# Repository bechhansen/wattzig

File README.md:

# WattZig - The Open Zigbee Power Meter

A Zigbee-based smart power meter reader for ESP32C6 that reads 3-phase electrical data via DLMS protocol and reports measurements to Zigbee hubs (Home Assistant, etc.).

## Overview

WattZig reads meter data via DLMS protocol over UART and reports 3-phase electrical measurements (voltage, current, active/reactive power, power factor, energy counters) through ZHA-compliant Zigbee clusters.

*The WattZig device reporting real-time electrical measurements to Home Assistant via Zigbee. All three phases show voltage (~228-230V), current (0.0-0.7A), power (9.0-130W), and power factor (11%-86%). The device also reports total energy consumption (34,351.77 kWh delivered) and can be integrated into automations and dashboards.*

## Features

- **3-Phase Metering**: Voltage, current, active/reactive power, power factor (phases A, B, C)
- **Energy Tracking**: Import/export energy counters with reporting
- **Zigbee ZHA**: Home Assistant integration via standard clusters
- **DLMS Parser**: State machine-based protocol handler at 2400 baud
- **Low Power**: FreeRTOS task design with Zigbee sleep support
- **Auto-Commissioning**: Network steering on first start
- **Status LEDs**: Green (data transmission), Red (commissioning)
- **Button Controls**: Long press (4s) = factory reset, double-click = restart

## Hardware Requirements

- **Microcontroller**: ESP32C6 (required for Zigbee)
- **ESP-IDF**: v5.5.2 (exact version)
- **Power Supply**: ≥4.5V input, MCP1700-3302E 3.3V regulator, 470µF–1000µF bulk capacitor (parallel to regulator)
- **UART1** (DLMS): TX=GPIO0, RX=GPIO1, 2400 baud, 8 bits, no parity
- **Peripherals**: GPIO5=Red LED, GPIO6=Green LED, GPIO4=Button

See [HARDWARE.md](HARDWARE.md) for complete Bill of Materials, schematics, and assembly instructions.

## Software Requirements

- **ESP-IDF v5.5.2**: `git clone -b v5.5.2 https://github.com/espressif/esp-idf.git && ./install.sh && source export.sh`
- **Dependencies** (auto-installed):
  - `espressif/esp-zigbee-lib` (~1.6.8)
  - `espressif/esp-zboss-lib` (~1.6.4)
  - `espressif/button` (2.4.1)

## Installation & Setup

1. **Clone and configure:**
   ```bash
   git clone <repo-url>
   cd wattzig/Software
   idf.py menuconfig
   ```

2. **Required menuconfig settings:**
   - `Component Config > Zigbee > Enable Zigbee Stack`
   - `Component Config > Zigbee > Device Type > End Device`
   - `Component Config > Power Management > Enable Power Management`

3. **Build and flash:**
   ```bash
   idf.py build
   idf.py -p /dev/ttyUSB0 -b 115200 flash
   idf.py -p /dev/ttyUSB0 monitor  # Exit: Ctrl+T then X
   ```

   See [FLASHING.md](FLASHING.md) for detailed hardware setup, boot mode configuration, and troubleshooting.

## Usage

**First Start:**
1. Device boots and performs factory reset
2. LED blinks (commissioning mode)
3. Device joins nearest Zigbee network via network steering
4. LED on briefly, then off
5. UART task starts reading meter data

**Normal Operation:**
- Device loads saved network config
- UART reads DLMS frames from meter
- Parsed data updates Zigbee cluster attributes
- Energy counters trigger ZCL reports

**Zigbee Endpoint 10:**
- Basic Cluster (0x0000): Device info
- Identify Cluster (0x0003): Identification
- Electrical Measurement (0x0B04): Voltage, current, power, power factor (all phases)
- Metering Cluster (0x0702): Energy delivered/received

## Configuration

Edit [Software/main/main.h](Software/main/main.h) for:
```c
#define ENDPOINT_ID 10                    // Zigbee endpoint
#define UART_NUM UART_NUM_1               // UART peripheral
#define UART_BAUD_RATE 2400               // Meter communication speed
#define LED_PIN 5                         // Red status LED
#define LED_PIN2 6                        // Green status LED
#define ED_AGING_TIMEOUT ESP_ZB_ED_AGING_TIMEOUT_64MIN
#define ED_KEEP_ALIVE 3000                // Keep-alive interval (ms)
```

## Debugging

### Enable Debug Logging
```c
// In app_main(), modify:
esp_log_level_set("Parser", ESP_LOG_DEBUG);  // Enable DLMS parser logs
esp_log_level_set("*", ESP_LOG_INFO);         // General logs
```

## References

- [ESP-IDF v5.5.2 Documentation](https://docs.espressif.com/projects/esp-idf/en/v5.5.2/)
- [Zigbee Cluster Library (ZCL)](https://zigbeealliance.org/)
- [Zigbee Cluster Library Specification](https://zigbeealliance.org/wp-content/uploads/2019/12/07-5123-06-zigbee-cluster-library-specification.pdf)
- [DLMS/COSEM Protocol](https://www.dlms.com/)
- [Home Assistant ZHA Integration](https://www.home-assistant.io/integrations/zha/)

## License

This project is licensed under the **GNU General Public License v3 (GPLv3)**.

You are free to use, modify, and distribute this software under the following conditions:
- Any derivative works must also be released under GPLv3
- You must provide access to the source code
- You must include this license and attribution
- You cannot create proprietary closed-source versions

See [LICENSE](LICENSE) for full details.

**GPLv3 ensures that improvements and modifications remain open source for the entire community.**

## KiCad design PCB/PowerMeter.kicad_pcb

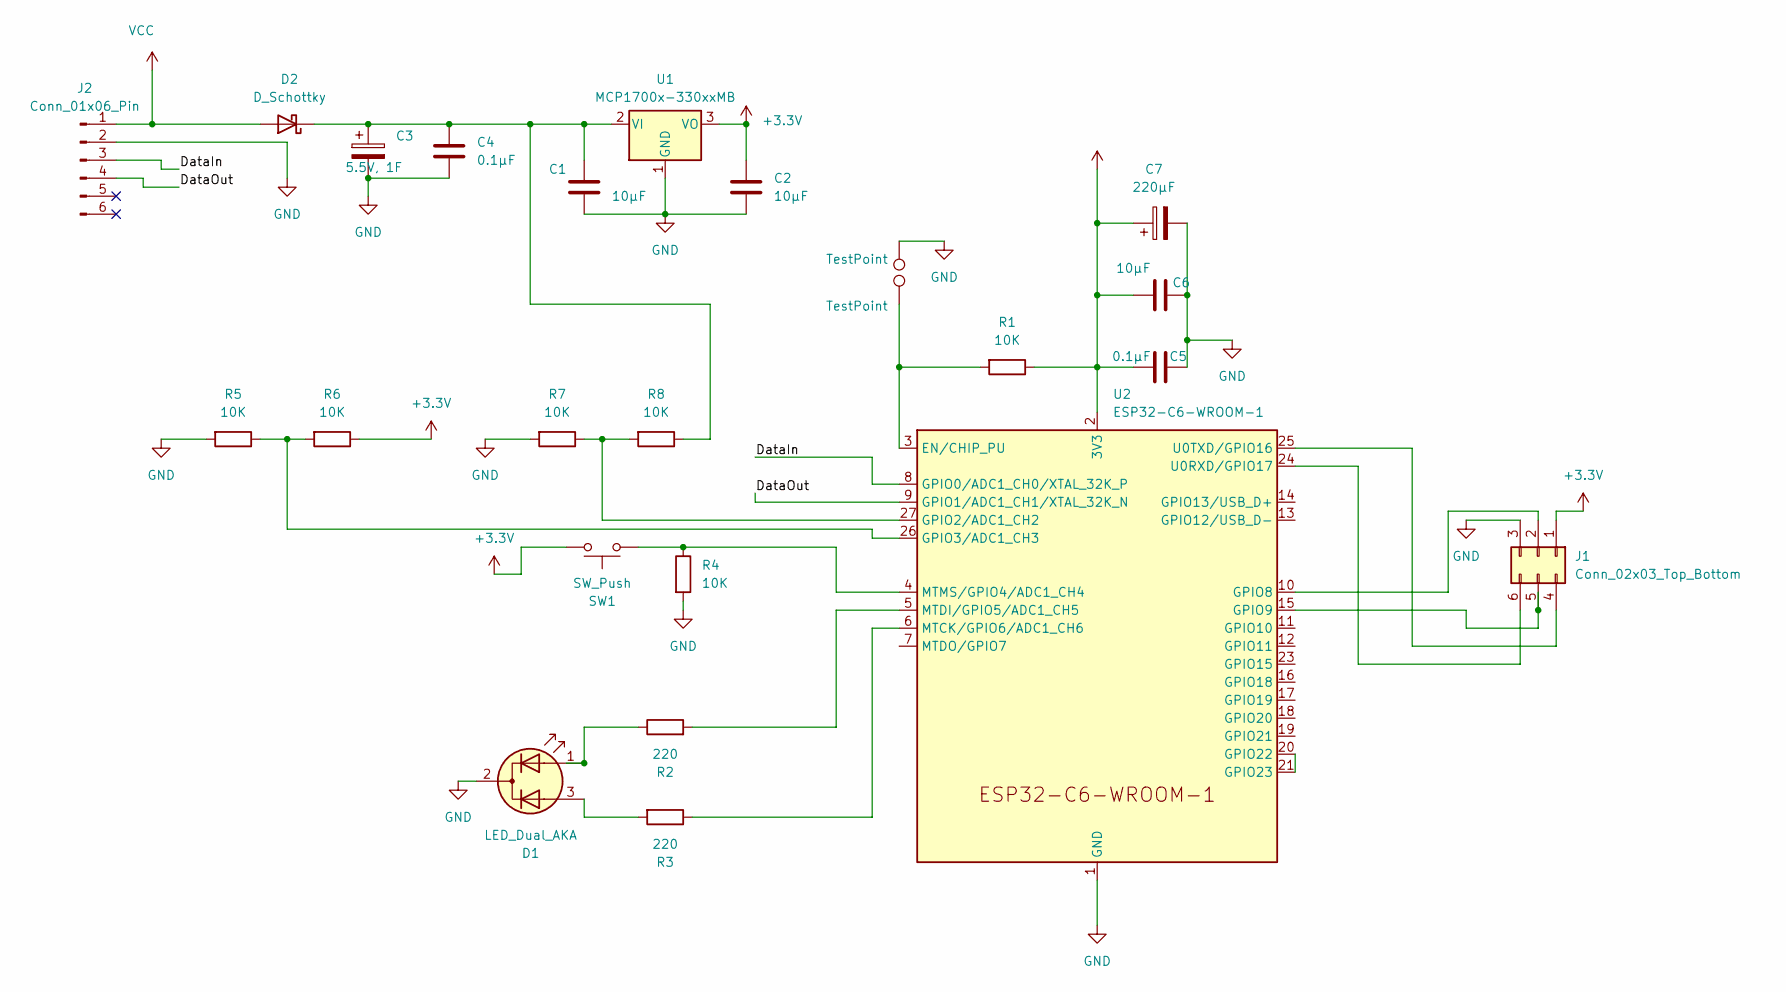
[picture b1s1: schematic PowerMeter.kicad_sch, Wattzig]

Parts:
C1, C2, C6: 10μF; C_0805_2012Metric_Pad1.18x1.45mm_HandSolder
C3: 5.5V, 1F; PHV-5R4H155-R
C4, C5: 0.1μF; C_0805_2012Metric_Pad1.18x1.45mm_HandSolder
C7: 220µF; C_1812_4532Metric
D1: LED_Dual_AKA; LED_D5.0mm-3
D2: D_Schottky; Nexperia_CFP3_SOD-123W
J1: Conn_02x03_Top_Bottom; PinHeader_2x03_P2.54mm_Vertical
J2: Conn_01x06_Pin; PinSocket_2x03_P2.54mm_Horizontal
R1, R4, R5, R6, R7, R8: 10K; R_0805_2012Metric_Pad1.20x1.40mm_HandSolder
R2, R3: 220; R_0805_2012Metric_Pad1.20x1.40mm_HandSolder
RST1, RST2: TestPoint; TestPoint_Pad_D2.0mm
SW1: SW_Push; CS1102V1135F160_pbh
U1: MCP1700x-330xxMB; SOT-89-3
U2: ESP32-C6-WROOM-1

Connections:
+3.3V: C2.1, C5.1, C6.1, C7.1, J1.1, R1.1, R6.1, SW1.1, U1.3 (VO), U2.2 (3V3)
/DataIn: J2.3, U2.8 (GPIO0/ADC1_CH0/XTAL_32K_P)
/DataOut: J2.4, U2.9 (GPIO1/ADC1_CH1/XTAL_32K_N)
GND: C1.2, C2.2, C3.2, C4.2, C5.2, C6.2, C7.2, D1.2 (K), J1.3, J2.2, R4.2, R5.2, R7.2, RST1.1, U1.1 (GND), U2.1 (GND), U2.28 (GND), U2.29 (GND)
unnamed: D1.1 (A1), R2.1
unnamed: D1.3 (A2), R3.2
unnamed: C1.1, C3.1, C4.1, D2.1 (K), R8.1, U1.2 (VI)
unnamed: J1.2, U2.10 (GPIO8)
unnamed: J1.4, U2.25 (U0TXD/GPIO16)
unnamed: J1.5, U2.15 (GPIO9)
unnamed: J1.6, U2.24 (U0RXD/GPIO17)
unnamed: R1.2, RST2.1, U2.3 (EN/CHIP_PU)
unnamed: R7.1, R8.2, U2.27 (GPIO2/ADC1_CH2)
unnamed: R5.1, R6.2, U2.26 (GPIO3/ADC1_CH3)
unnamed: U2.20 (GPIO22), U2.21 (GPIO23)
unnamed: R3.1, U2.6 (MTCK/GPIO6/ADC1_CH6)
unnamed: R2.2, U2.5 (MTDI/GPIO5/ADC1_CH5)
unnamed: R4.1, SW1.2, U2.4 (MTMS/GPIO4/ADC1_CH4)
VCC: D2.2 (A), J2.1

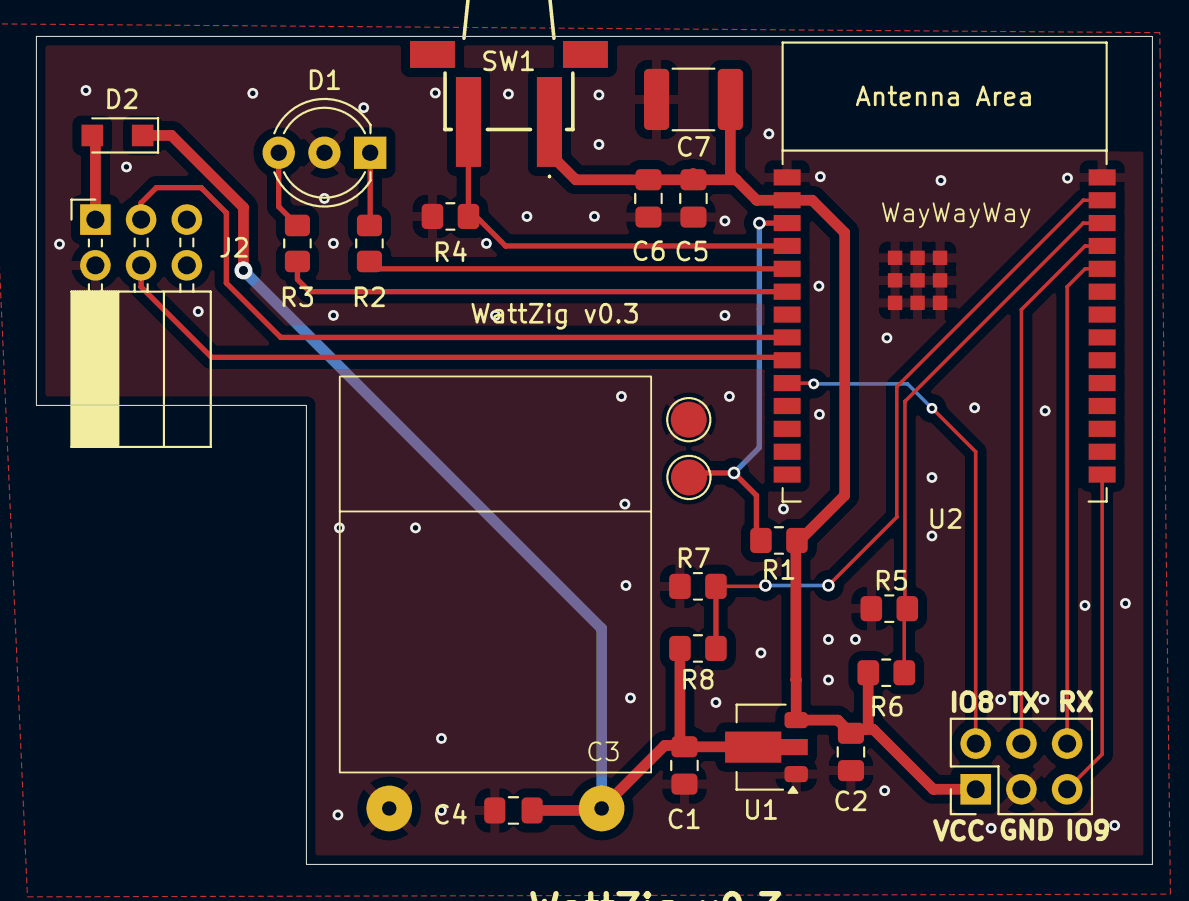
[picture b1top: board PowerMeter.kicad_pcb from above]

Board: 2 copper layers, 62.0 x 46.0 mm, 24 parts (0 on the bottom side), 19 nets.

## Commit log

2026-01-08 Initial public release
2026-01-08 Add images and descriptions to README for enhanced documentation
2026-01-09 Refactor ESP-IDF build step to use command directly instead of env variable
2026-01-09 Refine version generation to exclude pre-release tags
2026-01-09 Enhance version generation logic to handle tagged releases correctly
2026-01-10 Rename project from PowerMeter to WattZig and update related documentation and configurations
2026-01-11 Update README with additional badges for build status, latest release, license, ESP-IDF version, platform, Zigbee, and Home Assistant compatibility
2026-02-28 Added voltage measurement for 4.1 volt
